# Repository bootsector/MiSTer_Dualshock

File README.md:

# MiSTer_Dualshock
FPGA native serial Dualshock interface for MiSTer

This is a very simple Dualshock serial interface for MiSTer FPGA that allows 
you to play on MiSTer with your Sony Dualshock 1/2 controllers and other
compatible devices and adapters.

This relies on native low latency FPGA serial interface that, in order to work,
needs implementation of the SPI (low level) Dualshock (high level) protocol in
MiSTer cores.

An experimental MiSTer Game Boy core with support for this adapter can be found at https://github.com/bootsector/Gameboy_MiSTer/releases/tag/v0.1

BOM:

USB 3.0 A connector:
https://www.aliexpress.com/item/1997169684.html

Dualshock connector:
https://www.aliexpress.com/item/32818887920.html

DC (rumble) connector:
https://www.aliexpress.com/item/33005175186.html

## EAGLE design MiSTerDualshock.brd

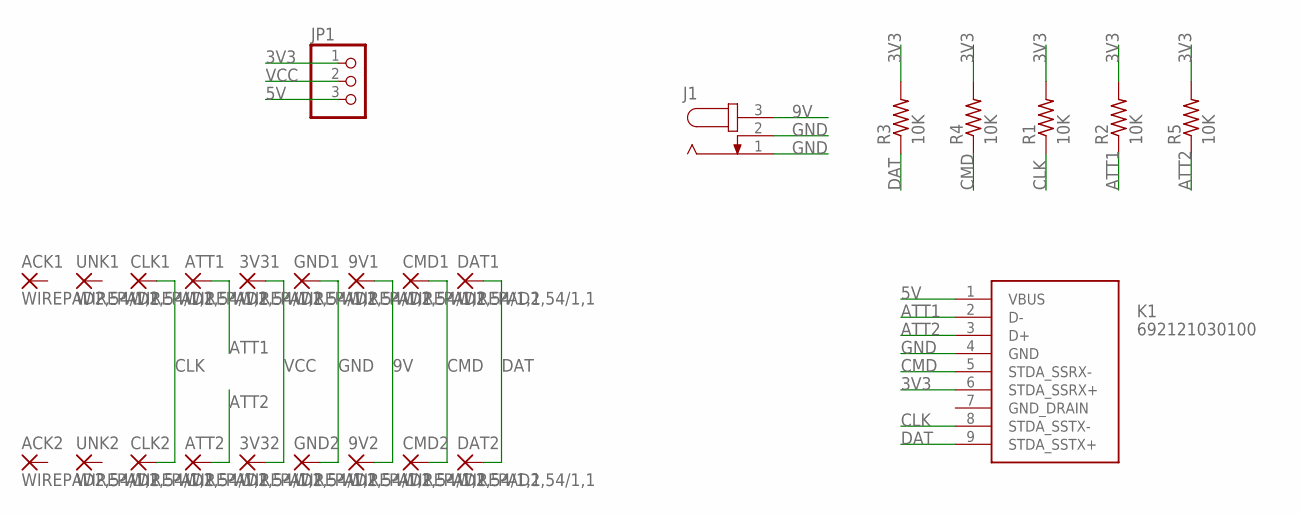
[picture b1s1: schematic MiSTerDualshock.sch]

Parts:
3V31, 3V32, 9V1, 9V2: WIREPAD2,54/1,1; 2,54/1,1
ACK1, ACK2: WIREPAD2,54/1,1; 2,54/1,1
ATT1, ATT2: WIREPAD2,54/1,1; 2,54/1,1
CLK1, CLK2: WIREPAD2,54/1,1; 2,54/1,1
CMD1, CMD2: WIREPAD2,54/1,1; 2,54/1,1
DAT1, DAT2: WIREPAD2,54/1,1; 2,54/1,1
GND1, GND2: WIREPAD2,54/1,1; 2,54/1,1
J1: JACK-PLUG1; SPC4078
JP1: PINHD-1X3; 1X03
K1: 692121030100
R1, R2, R3, R4, R5: 10K; 0207/10
UNK1, UNK2: WIREPAD2,54/1,1; 2,54/1,1

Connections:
3V3: JP1.1, K1.6 (STDA_SSRX+), R1.2, R2.2, R3.2, R4.2, R5.2
5V: JP1.3, K1.1 (VBUS)
9V: 9V1.1, 9V2.1, J1.3
ATT1: ATT1.1, K1.2 (D-), R2.1
ATT2: ATT2.1, K1.3 (D+), R5.1
CLK: CLK1.1, CLK2.1, K1.8 (STDA_SSTX-), R1.1
CMD: CMD1.1, CMD2.1, K1.5 (STDA_SSRX-), R4.1
DAT: DAT1.1, DAT2.1, K1.9 (STDA_SSTX+), R3.1
GND: GND1.1, GND2.1, J1.1, J1.2, K1.4 (GND)
VCC: 3V31.1, 3V32.1, JP1.2

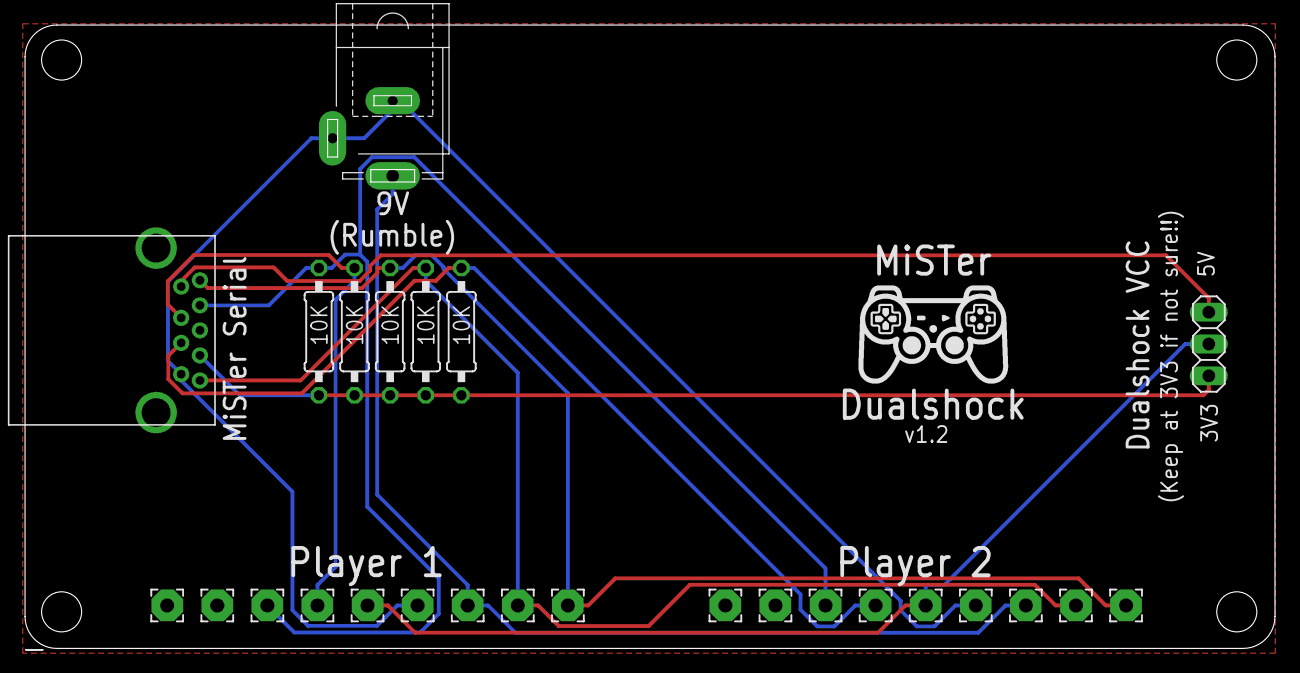
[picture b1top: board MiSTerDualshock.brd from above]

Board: 2 copper layers, 99.8 x 49.8 mm, 26 parts (0 on the bottom side), 10 nets.

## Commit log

2019-06-23 Adding image to Readme
2019-06-23 Added pull-up resistor to DAT line
2019-06-24 Version 1.2

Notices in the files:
parts and their libraries:
wuerth: Copyright: Würth Elektronik
